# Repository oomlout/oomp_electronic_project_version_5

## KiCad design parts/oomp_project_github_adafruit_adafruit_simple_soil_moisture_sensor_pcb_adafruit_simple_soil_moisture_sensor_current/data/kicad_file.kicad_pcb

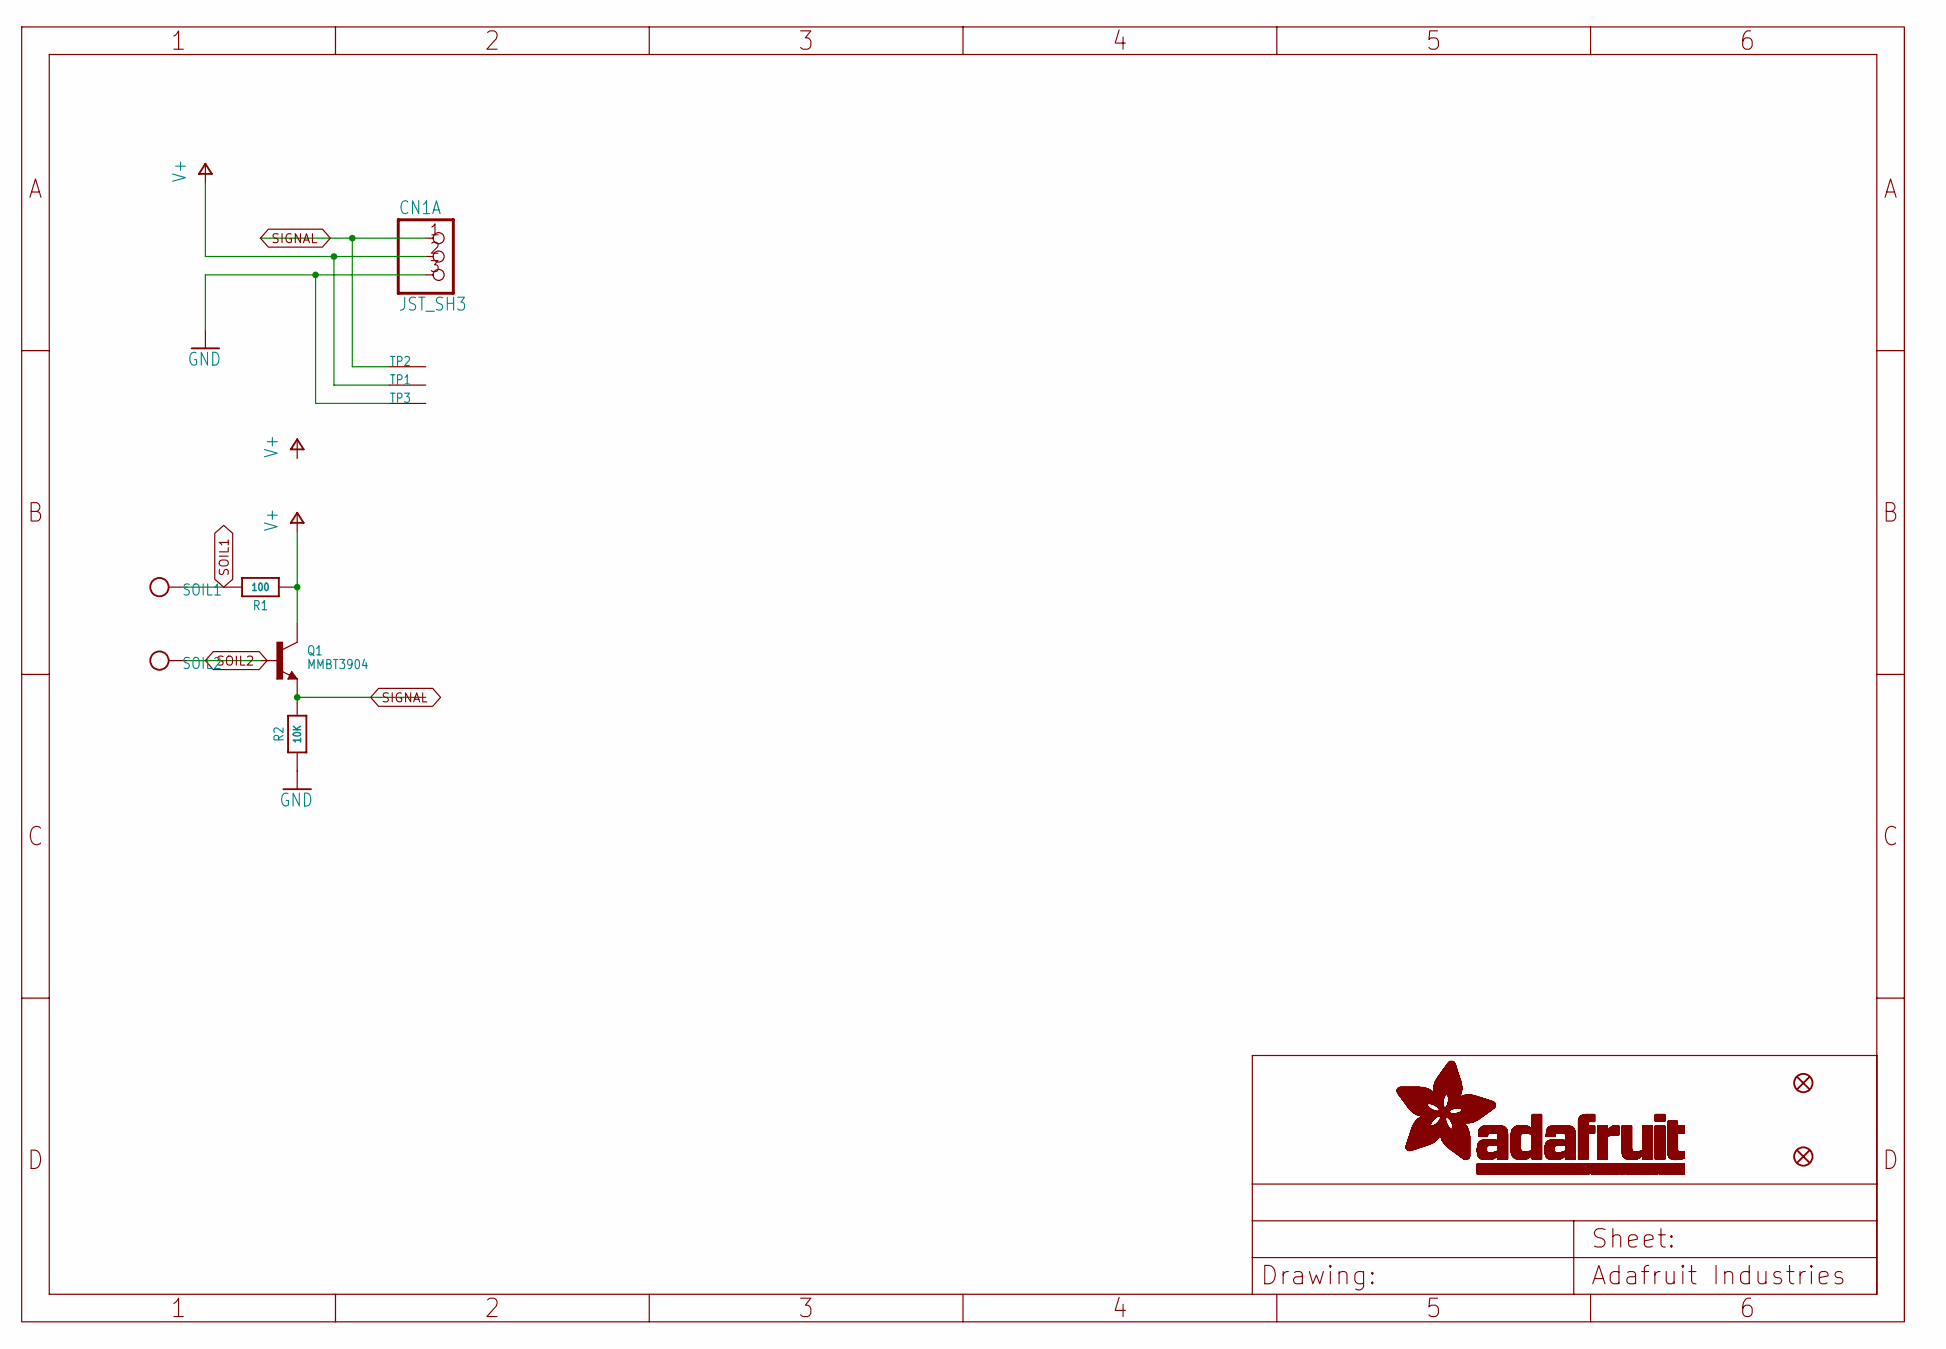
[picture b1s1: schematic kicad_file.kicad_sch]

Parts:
CN1: JST_SH3
Q1: MMBT3904; SOT23-WIDE
R1: 100; 0805-NO
R2: 10K; 0805-NO
SOIL1, SOIL2: TESTPOINTROUND2MMNO; TESTPOINT_ROUND_2MM_NO
TP1, TP2, TP3: SEWTAPPCB_ALLIGATOR; PCB_ALLI
U$2, U$3: FIDUCIAL_0.5MM

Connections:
GND: CN1.3, R2.1, TP3.P$1
SIGNAL: CN1.1, Q1.2 (E), R2.2, TP2.P$1
SOIL1: R1.2, SOIL1.P$1
SOIL2: Q1.1 (B), SOIL2.P$1
V+: CN1.2, Q1.3 (C), R1.1, TP1.P$1

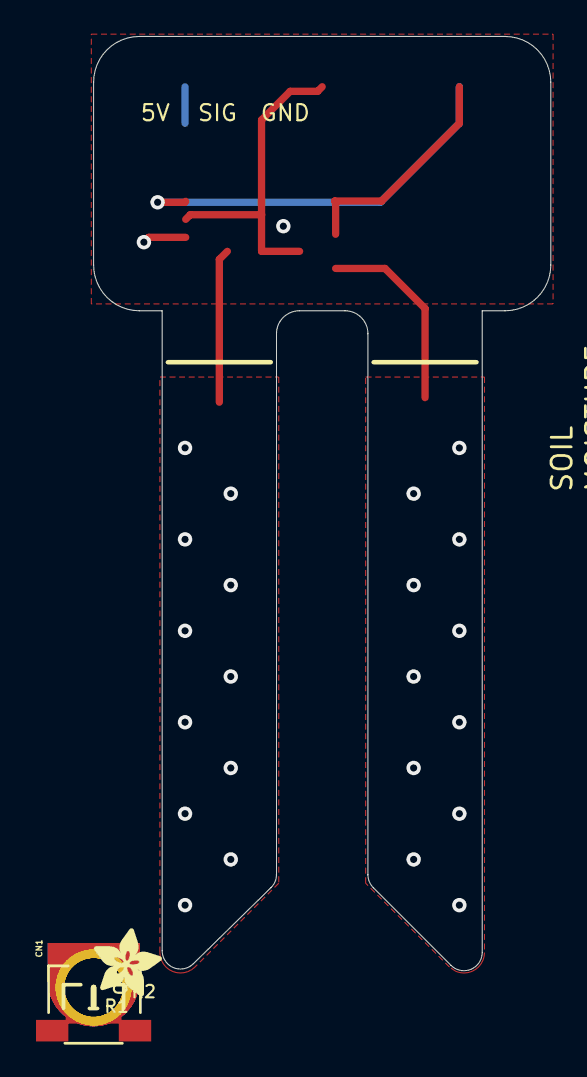
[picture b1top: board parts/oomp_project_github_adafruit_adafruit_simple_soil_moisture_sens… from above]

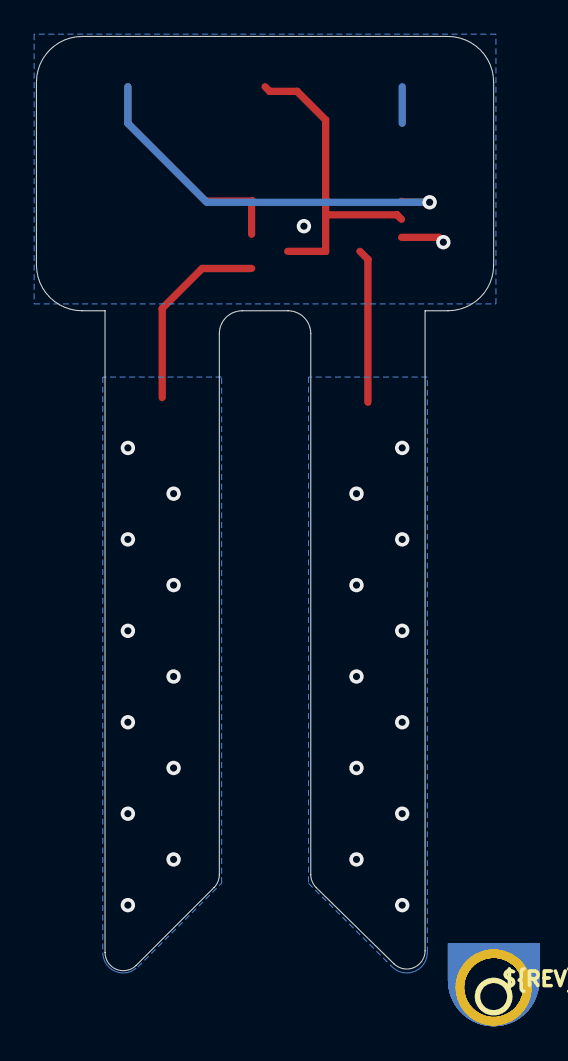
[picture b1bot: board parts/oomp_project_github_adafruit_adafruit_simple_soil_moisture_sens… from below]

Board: 16 copper layers, 25.4 x 51.9 mm, 21 parts (2 on the bottom side), 5 nets.

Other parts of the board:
PLABEL0: PLABEL0
PLABEL1: PLABEL1
PLABEL2: PLABEL2
PLABEL3: PLABEL3
PLABEL4: PLABEL4
PLABEL5: PLABEL5
PLABEL6: PLABEL6
PLABEL7: PLABEL7
U$1: ADAFRUIT_3.5MM
U$5: PCBFEAT-REV-040

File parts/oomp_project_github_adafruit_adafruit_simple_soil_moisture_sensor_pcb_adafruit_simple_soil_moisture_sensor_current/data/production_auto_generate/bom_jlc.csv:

Comment,Designator,Footprint,LCSC Part #
,U$1,Adafruit Simple Soil Moisture Sensor-import-fps:ADAFRUIT_3.5MM,
,U$5,Adafruit Simple Soil Moisture Sensor-import-fps:PCBFEAT-REV-040,
,PLABEL0,Adafruit Simple Soil Moisture Sensor-import-fps:PLABEL0,
,PLABEL1,Adafruit Simple Soil Moisture Sensor-import-fps:PLABEL1,
,PLABEL2,Adafruit Simple Soil Moisture Sensor-import-fps:PLABEL2,
,PLABEL3,Adafruit Simple Soil Moisture Sensor-import-fps:PLABEL3,
,PLABEL4,Adafruit Simple Soil Moisture Sensor-import-fps:PLABEL4,
,PLABEL5,Adafruit Simple Soil Moisture Sensor-import-fps:PLABEL5,
,PLABEL6,Adafruit Simple Soil Moisture Sensor-import-fps:PLABEL6,
,PLABEL7,Adafruit Simple Soil Moisture Sensor-import-fps:PLABEL7,
,"SOIL1,SOIL2",Adafruit Simple Soil Moisture Sensor-import-fps:TESTPOINT_ROUND_2MM_NO,
100,R1,Adafruit Simple Soil Moisture Sensor-import-fps:0805-NO,C17408
10K,R2,Adafruit Simple Soil Moisture Sensor-import-fps:0805-NO,C17414
FIDUCIAL_0.5MM,"U$2,U$3",Adafruit Simple Soil Moisture Sensor-import-fps:FIDUCIAL_0.5MM,
JST_SH3,CN1,Adafruit Simple Soil Moisture Sensor-import-fps:JST_SH3,
MMBT3904,Q1,Adafruit Simple Soil Moisture Sensor-import-fps:SOT23-WIDE,

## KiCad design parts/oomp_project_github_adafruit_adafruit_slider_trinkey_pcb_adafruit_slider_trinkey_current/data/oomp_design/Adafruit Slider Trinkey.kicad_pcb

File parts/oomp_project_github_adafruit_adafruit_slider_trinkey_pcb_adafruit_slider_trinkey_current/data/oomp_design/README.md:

# OOMP KiCad design copy

Open `Adafruit Slider Trinkey.kicad_pro` (or the `.kicad_pcb` / `.kicad_sch`) in KiCad. Local OOMP libraries are under `libraries/`. Original inputs are preserved in [../original/](../original/).

Only verified unchanged installed KiCad defaults were renamed. Modified, custom, unmatched and unavailable items remain unchanged. Soldering variants are never swapped during conversion. Existing pad coordinates, nets and UUIDs are preserved.

See [conversion_report.yaml](conversion_report.yaml) for every conversion and skip. Copy this directory before editing; regeneration refuses to overwrite edited design files.

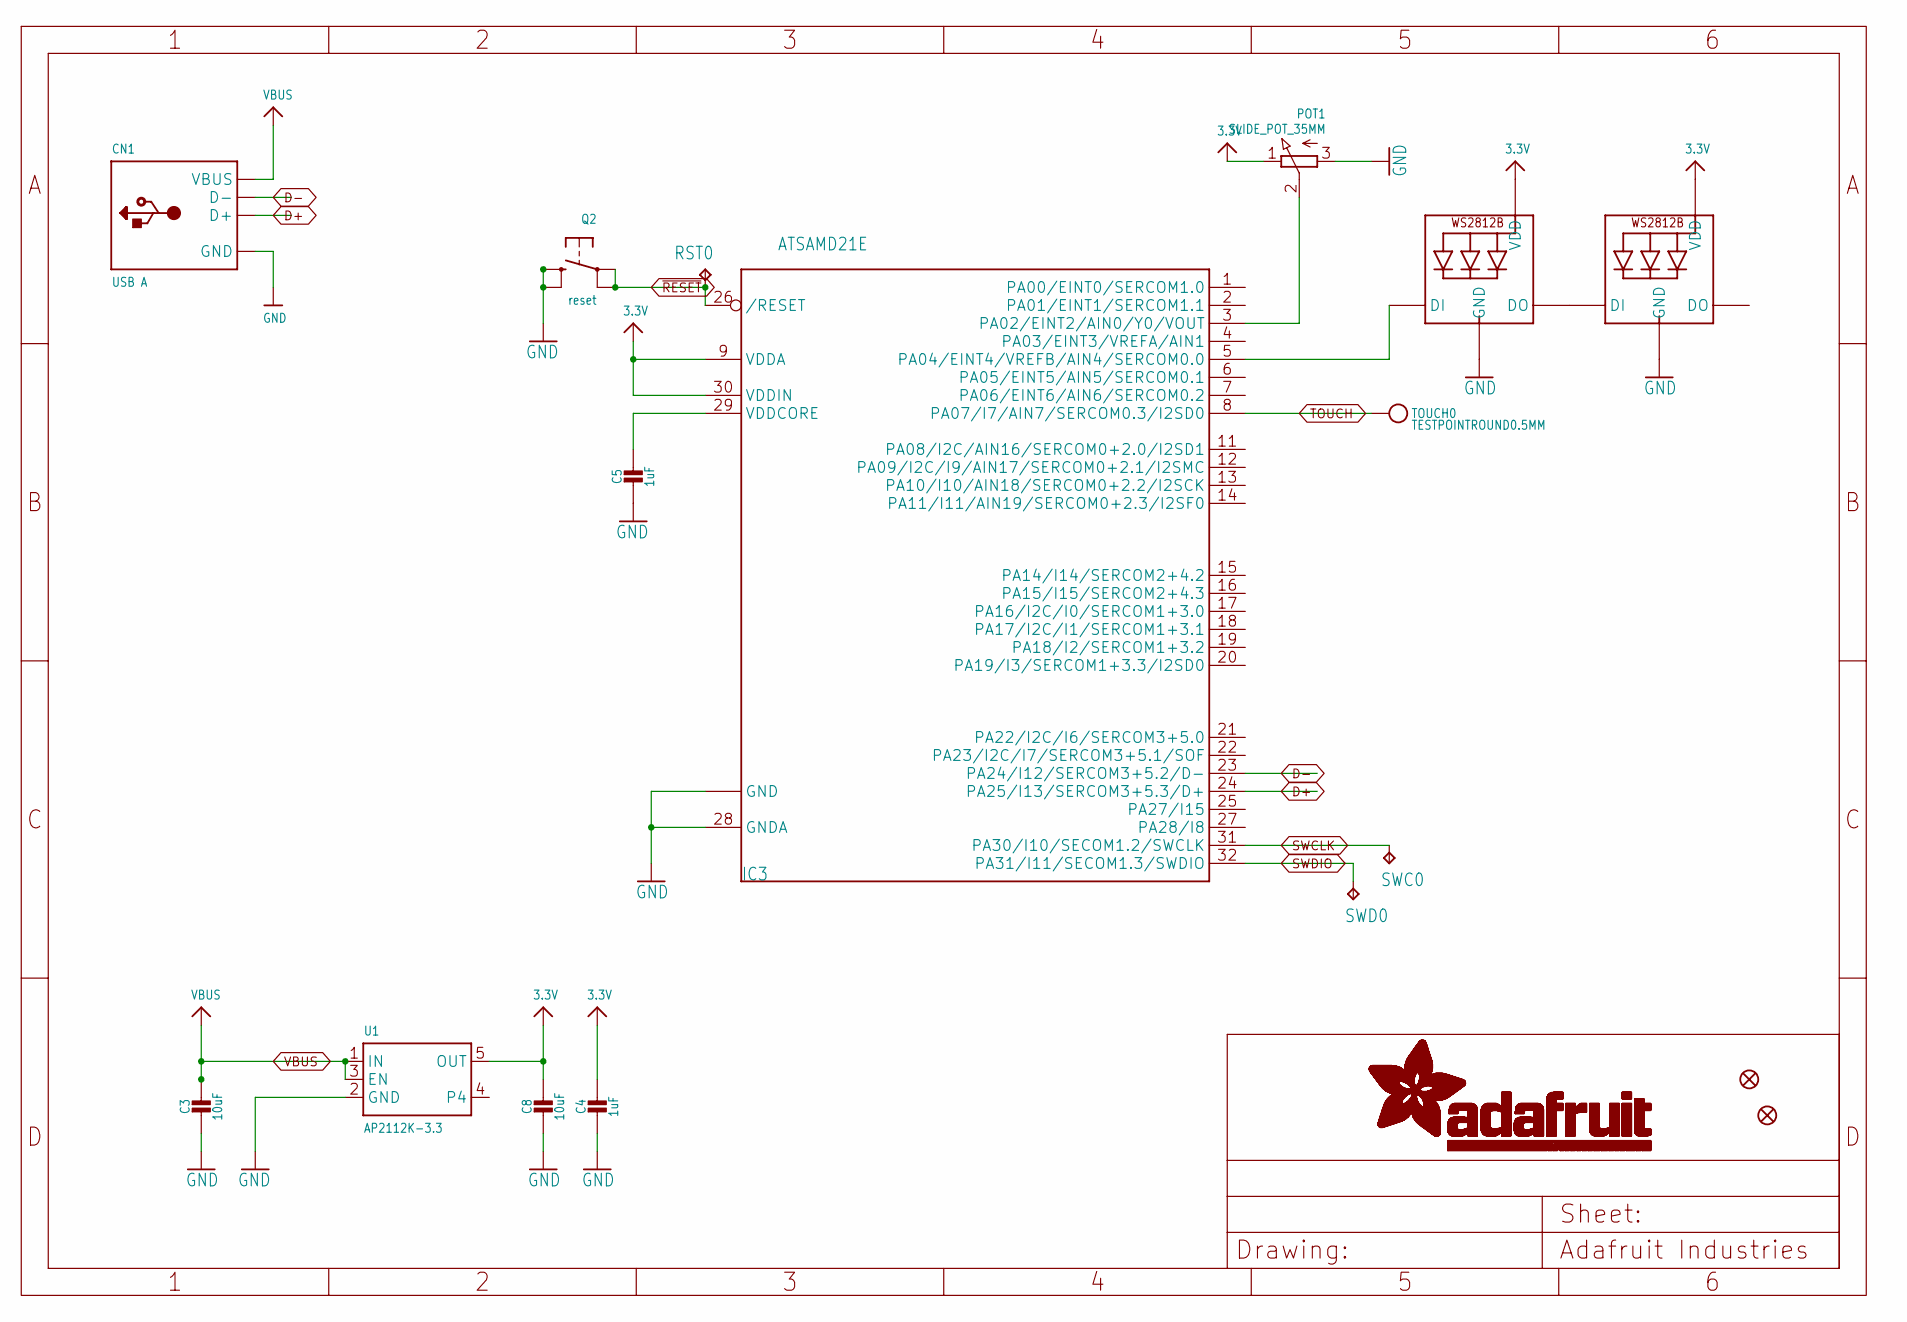
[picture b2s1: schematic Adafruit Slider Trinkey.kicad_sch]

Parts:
C3, C8: 10uF; 0805-NO
C4, C5: 1uF; 0603-NO
CN1: USB A; USBA_PCB
FID1, FID2: FIDUCIAL_1MM
IC3: ATSAMD21E; QFN32_5MM
LED1, LED2: WS2812B_SK6812E; NEO3535_REVERSE
POT1: SLIDE_POT_35MM
Q2: reset; BTN_KMR2_4.6X2.8
RST0: TPTP16R; TP16R
SWC0: TPTP15R; TP15R
SWD0: TPTP16R; TP16R
TOUCH0: TESTPOINTROUND0.5MM; TESTPOINT_ROUND_0.5MM
U1: AP2112K-3.3; SOT23-5

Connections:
3.3V: C4.1, C8.1, IC3.9 (VDDA), IC3.30 (VDDIN), LED1.1-VDD (VDD), LED2.1-VDD (VDD), POT1.1 (E), U1.5 (OUT)
D+: CN1.USB_PLUS (D+), IC3.24 (PA25/I13/SERCOM3+5.3/D+)
D-: CN1.USB_NEG (D-), IC3.23 (PA24/I12/SERCOM3+5.2/D-)
GND: C3.2, C4.2, C5.2, C8.2, CN1.GND, IC3.10 (GND), IC3.28 (GNDA), IC3.33 (GND), LED1.3-GND (GND), LED2.3-GND (GND), POT1.3 (A), Q2.B (S), Q2.B' (S1), U1.2 (GND)
unnamed: IC3.5 (PA04/EINT4/VREFB/AIN4/SERCOM0.0), LED1.4-DIN (DI)
unnamed: LED1.2-DOUT (DO), LED2.4-DIN (DI)
POT: IC3.3 (PA02/EINT2/AIN0/Y0/VOUT), POT1.2 (S)
SWCLK: IC3.31 (PA30/I10/SECOM1.2/SWCLK), SWC0.TP
SWDIO: IC3.32 (PA31/I11/SECOM1.3/SWDIO), SWD0.TP
TOUCH: IC3.8 (PA07/I7/AIN7/SERCOM0.3/I2SD0), TOUCH0.P$1
VBUS: C3.1, CN1.VCC (VBUS), U1.1 (IN), U1.3 (EN)
VDDCORE1: C5.1, IC3.29 (VDDCORE)
~RESET: IC3.26 (/RESET), Q2.A, Q2.A' (P1), RST0.TP

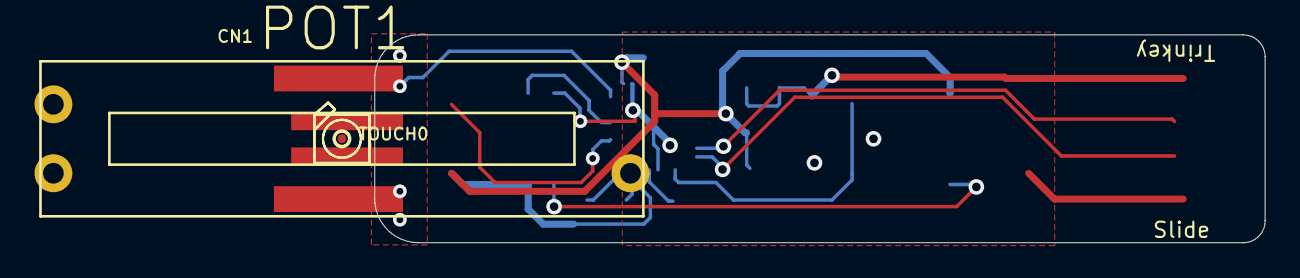
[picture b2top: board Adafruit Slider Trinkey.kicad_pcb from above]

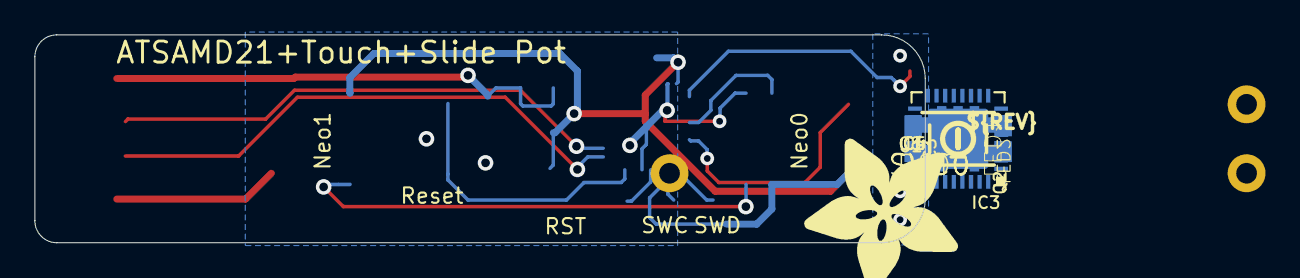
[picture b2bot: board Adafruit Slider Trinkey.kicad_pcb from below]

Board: 2 copper layers, 51.7 x 12.1 mm, 19 parts (14 on the bottom side), 13 nets.

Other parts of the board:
U$6: ADAFRUIT_9MM
U$8: PCBFEAT-REV-040

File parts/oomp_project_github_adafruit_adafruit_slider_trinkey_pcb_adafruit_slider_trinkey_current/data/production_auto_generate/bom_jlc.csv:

Comment,Designator,Footprint,LCSC Part #
,U$6,Adafruit Slider Trinkey-import-fps:ADAFRUIT_9MM,
,U$8,Adafruit Slider Trinkey-import-fps:PCBFEAT-REV-040,
,TOUCH0,Adafruit Slider Trinkey-import-fps:TESTPOINT_ROUND_0.5MM,
10uF,"C3,C8",Adafruit Slider Trinkey-import-fps:0805-NO,
1uF,"C4,C5",Adafruit Slider Trinkey-import-fps:0603-NO,C5673
AP2112K-3.3,U1,Adafruit Slider Trinkey-import-fps:SOT23-5,
ATSAMD21E,IC3,Adafruit Slider Trinkey-import-fps:QFN32_5MM,
reset,Q2,Adafruit Slider Trinkey-import-fps:BTN_KMR2_4.6X2.8,
SLIDE_POT_35MM,POT1,Adafruit Slider Trinkey-import-fps:SLIDE_POT_35MM,
TPTP15R,SWC0,Adafruit Slider Trinkey-import-fps:TP15R,
TPTP16R,"RST0,SWD0",Adafruit Slider Trinkey-import-fps:TP16R,
USB A,CN1,Adafruit Slider Trinkey-import-fps:USBA_PCB,
WS2812B_SK6812E,"LED1,LED2",Adafruit Slider Trinkey-import-fps:NEO3535_REVERSE,

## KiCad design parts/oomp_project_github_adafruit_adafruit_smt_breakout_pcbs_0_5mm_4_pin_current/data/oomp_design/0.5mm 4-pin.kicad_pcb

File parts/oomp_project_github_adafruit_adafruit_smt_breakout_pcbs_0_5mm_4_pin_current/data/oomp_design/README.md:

# OOMP KiCad design copy

Open `0.5mm 4-pin.kicad_pro` (or the `.kicad_pcb` / `.kicad_sch`) in KiCad. Local OOMP libraries are under `libraries/`. Original inputs are preserved in [../original/](../original/).

Only verified unchanged installed KiCad defaults were renamed. Modified, custom, unmatched and unavailable items remain unchanged. Soldering variants are never swapped during conversion. Existing pad coordinates, nets and UUIDs are preserved.

See [conversion_report.yaml](conversion_report.yaml) for every conversion and skip. Copy this directory before editing; regeneration refuses to overwrite edited design files.

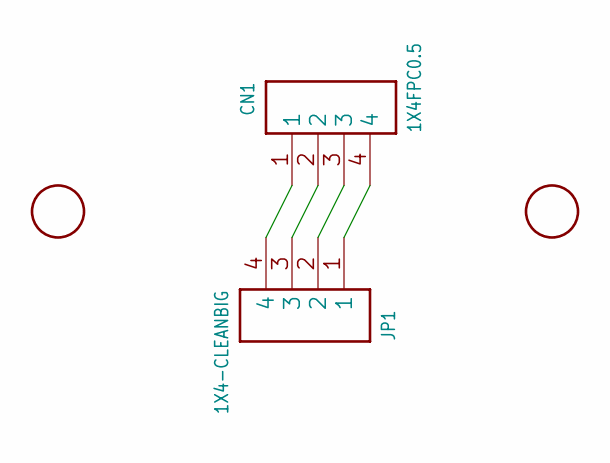
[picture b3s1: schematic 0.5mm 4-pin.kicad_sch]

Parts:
CN1: 1X4FPC0.5; FPC_0.5MM-4
JP1: 1X4-CLEANBIG; 1X04-CLEANBIG
U$2, U$3: FIDUCIAL; FIDUCIAL_1MM

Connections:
unnamed: CN1.4, JP1.1
unnamed: CN1.3, JP1.2
unnamed: CN1.2, JP1.3
unnamed: CN1.1, JP1.4

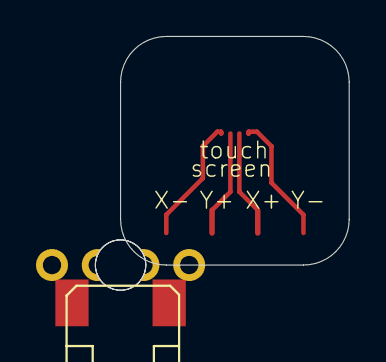
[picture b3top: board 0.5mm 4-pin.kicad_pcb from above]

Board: 16 copper layers, 12.7 x 12.7 mm, 7 parts (1 on the bottom side), 4 nets.

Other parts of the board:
U$1: ADAFRUIT200MIL
UNK_HOLE_0: dummyfp0
UNK_HOLE_1: dummyfp1

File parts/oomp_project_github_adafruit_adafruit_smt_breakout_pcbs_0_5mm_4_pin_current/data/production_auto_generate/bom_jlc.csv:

Comment,Designator,Footprint,LCSC Part #
,U$1,0.5mm 4-pin-import-fps:ADAFRUIT200MIL,
1X4-CLEANBIG,JP1,0.5mm 4-pin-import-fps:1X04-CLEANBIG,C42431795
1X4FPC0.5,CN1,0.5mm 4-pin-import-fps:FPC_0.5MM-4,
FIDUCIAL,"U$2,U$3",0.5mm 4-pin-import-fps:FIDUCIAL_1MM,

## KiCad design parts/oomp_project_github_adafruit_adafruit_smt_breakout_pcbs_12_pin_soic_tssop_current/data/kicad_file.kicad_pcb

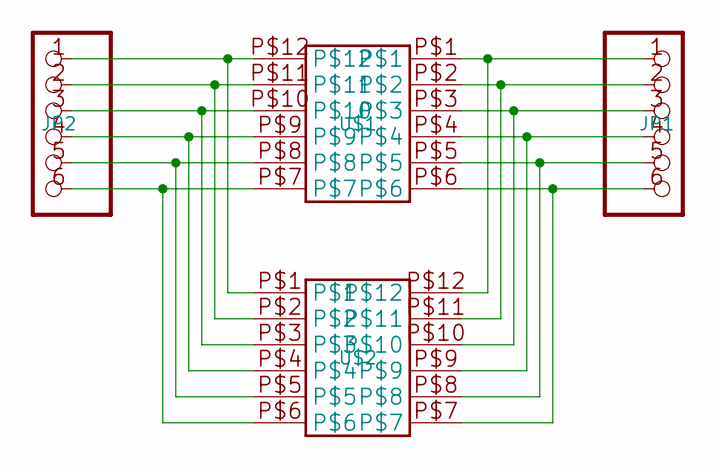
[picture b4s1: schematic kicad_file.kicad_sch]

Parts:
JP1, JP2: PADS-6
U$1: 12-PINTSSOP-NW; TSSOP12-NW
U$2: 12-PINSOIC-NW; SO12-NW

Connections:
unnamed: JP2.2, U$1.P$11, U$2.P$2
unnamed: JP2.3, U$1.P$10, U$2.P$3
unnamed: JP2.4, U$1.P$9, U$2.P$4
unnamed: JP2.5, U$1.P$8, U$2.P$5
unnamed: JP2.6, U$1.P$7, U$2.P$6
unnamed: JP1.1, U$1.P$1, U$2.P$12
unnamed: JP1.2, U$1.P$2, U$2.P$11
unnamed: JP1.3, U$1.P$3, U$2.P$10
unnamed: JP1.4, U$1.P$4, U$2.P$9
unnamed: JP1.5, U$1.P$5, U$2.P$8
unnamed: JP1.6, U$1.P$6, U$2.P$7
unnamed: JP2.1, U$1.P$12, U$2.P$1

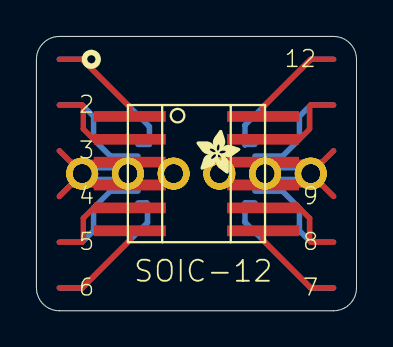
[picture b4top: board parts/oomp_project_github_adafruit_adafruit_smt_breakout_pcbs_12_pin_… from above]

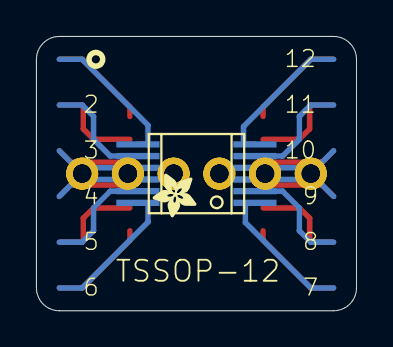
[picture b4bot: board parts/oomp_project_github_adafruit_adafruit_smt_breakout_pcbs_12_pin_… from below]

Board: 2 copper layers, 17.8 x 15.2 mm, 6 parts (2 on the bottom side), 12 nets.

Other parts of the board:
U$3, U$4: ADAFRUIT_2.5MM

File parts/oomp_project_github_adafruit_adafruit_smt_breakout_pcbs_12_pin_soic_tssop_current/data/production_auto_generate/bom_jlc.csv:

Comment,Designator,Footprint,LCSC Part #
,"U$3,U$4",12-pin SOIC+TSSOP-import-fps:ADAFRUIT_2.5MM,
,"JP1,JP2",12-pin SOIC+TSSOP-import-fps:PADS-6,
12-PINSOIC-NW,U$2,12-pin SOIC+TSSOP-import-fps:SO12-NW,
12-PINTSSOP-NW,U$1,12-pin SOIC+TSSOP-import-fps:TSSOP12-NW,
